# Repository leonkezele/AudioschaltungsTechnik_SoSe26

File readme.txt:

Bestellliste vom 22. 05. von Leon an Herr Tschirley
  - Bourns PTA4543-2015CPA103 - Fader: 10k log (Mouser Nr. 652-PTA4543-10K) mid. 10 Sück
  - Poti Alps RK09K 100k Single (Mouser Nr. 688-RK09K110K15C0104) mind. 10 Stück
  - Poti Alps RK09L 10k Dual (Mouser Nr. 688-RK09L1140A5E) mind. 30 Stück
  - J111 SOT23 (Mouser Nr. 512-MMBFJ111) mind. 10 Stück
  - 2917 Tantalelko 100u (mouser Nr. 80-T491D107K004) mind. 10 Stück
  - NE5532 SOIC-8 (Mouser Nr. 595-NE5532DR) (75 Stück)
  - LED THT mit V_f=3V (Mouser Nr. 941-C503BBANCY0C0462) (10 Stück)
  - Diode LL4148 Mini-MELF (Mouser Nr. 821-LL4148L0G) (20 Stück)
  - Schottky-Diode SOD-123: 1N5819HW (Mouser Nr. 621-1N5819HW-F) (20 Stück)

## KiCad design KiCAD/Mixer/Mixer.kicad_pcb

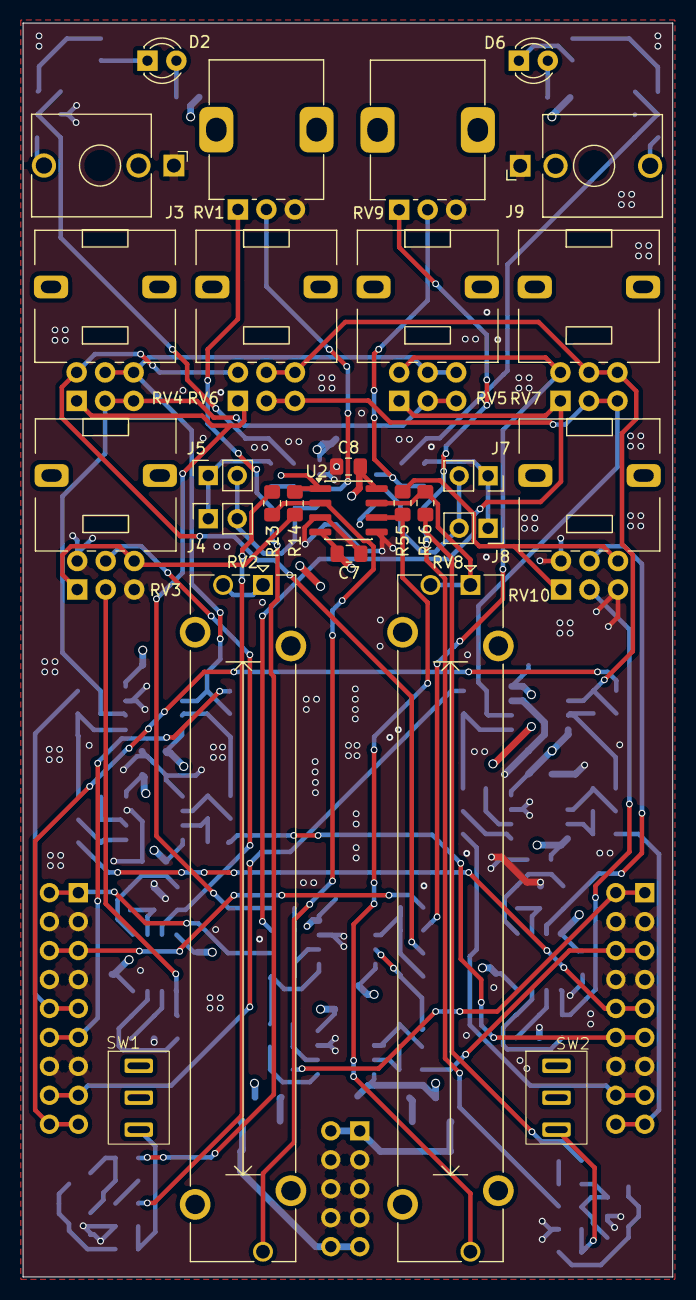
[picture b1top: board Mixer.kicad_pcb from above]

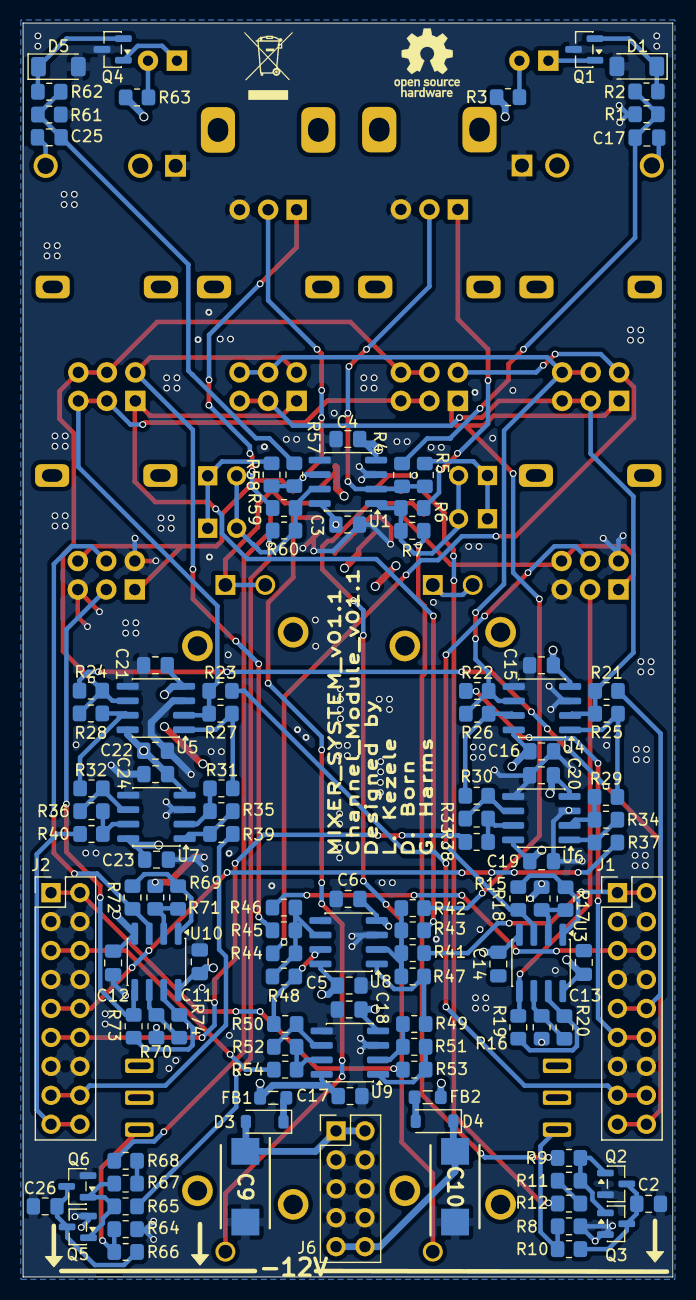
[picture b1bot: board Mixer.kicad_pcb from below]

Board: 4 copper layers, 57.0 x 110.0 mm, 145 parts (118 on the bottom side), 95 nets.

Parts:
C2, C26: 220n; C_0805_2012Metric_Pad1.18x1.45mm_HandSolder
C3, C4, C5, C6, C7, C8, C11, C12, C13, C14, C15, C16, C17, C18, C19, C20, C21, C22, C23, C24: 100n; C_0805_2012Metric_Pad1.18x1.45mm_HandSolder
C9, C10: 100u; CAPPM7343X310N
C17#2, C25: 2u; C_0805_2012Metric_Pad1.18x1.45mm_HandSolder
D1, D5: 1N4148; D_MiniMELF
D2, D6: LED; LED_D3.0mm
D3, D4: 1N5711; D_SOD-123
FB1, FB2: FerriteBead; L_0805_2012Metric_Pad1.05x1.20mm_HandSolder
J1, J2: Conn_02x09_Odd_Even; PinHeader_2x09_P2.54mm_Vertical
J3, J9: AudioJack2; Jack_3.5mm_QingPu_WQP-PJ398SM_Vertical_CircularHoles
J4, J5, J7, J8: Conn_01x02_Socket; PinSocket_1x02_P2.54mm_Vertical
J6: Conn_02x05_Odd_Even; PinHeader_2x05_P2.54mm_Vertical
Q1, Q4: NPN; SOT-23
Q2, Q3, Q5, Q6: MMBFJ111; SOT-23
R1, R61: 5k; R_0805_2012Metric_Pad1.20x1.40mm_HandSolder
R2, R10, R62, R66: 100k; R_0805_2012Metric_Pad1.20x1.40mm_HandSolder
R3, R63: 4,7k; R_0805_2012Metric_Pad1.20x1.40mm_HandSolder
R4, R57: 10K; R_0805_2012Metric_Pad1.20x1.40mm_HandSolder
R5, R58: 8k6; R_0805_2012Metric_Pad1.20x1.40mm_HandSolder
R6, R8, R13, R21, R22, R23, R24, R25, R26, R27, R28, R55, R59, R64: 10k; R_0805_2012Metric_Pad1.20x1.40mm_HandSolder
R7, R12, R14, R37, R38, R39, R40, R53, R54, R56, R60, R68: 0R; R_0805_2012Metric_Pad1.20x1.40mm_HandSolder
R9, R11, R65, R67: 2k2; R_0805_2012Metric_Pad1.20x1.40mm_HandSolder
R15, R16, R18, R19, R69, R70, R72, R73: 3k3; R_0805_2012Metric_Pad1.20x1.40mm_HandSolder
R17, R20, R29, R30, R31, R32, R33, R34, R35, R36, R41, R42, R43, R44, R45, R46, R47, R48, R49, R50, R51, R52, R71, R74: 1k; R_0805_2012Metric_Pad1.20x1.40mm_HandSolder
RV1, RV9: 100K; Potentiometer_Alps_RK09K_Single_Vertical
RV2: 10k; Potentiometer_Bourns_PTA4543_Single_Slide
RV3, RV4, RV5, RV6, RV7, RV10: 10k; Potentiometer_Alps_RK09L_Double_Vertical
RV8: R_Potentiometer; Potentiometer_Bourns_PTA4543_Single_Slide
SW1, SW2: SW_MEC_5G; Switch BHT
U1, U2, U3, U4, U5, U6, U7, U8, U9, U10: NE5532; SOIC-8_3.9x4.9mm_P1.27mm

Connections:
/Channel/+12V: C3.2, C5.2, C7.2, C11.2, C13.2, C15.2, C17.2, C19.2, C21.2, C23.2, FB1.1, R3.1, R63.1, U1.8 (V+), U2.4 (V-), U3.8 (V+), U4.4 (V-), U5.4 (V-), U6.8 (V+), U7.8 (V+), U8.8 (V+), U9.8 (V+), U10.8 (V+)
/Channel/-12V: C4.2, C6.2, C8.2, C12.2, C14.2, C16.2, C18.2, C20.2, C22.2, C24.2, FB2.2, SW1.1 (A), SW1.2 (A), SW2.1 (A), SW2.2 (A), U1.4 (V-), U2.8 (V+), U3.4 (V-), U4.8 (V+), U5.8 (V+), U6.4 (V-), U7.4 (V-), U8.4 (V-), U9.4 (V-), U10.4 (V-)
/Channel/Ch1_outL: R42.1, RV4.1, RV6.1
/Channel/Ch1_outR: R44.1, RV4.4, RV6.4
/Channel/Ch2_outL: R43.1, RV5.1, RV7.1
/Channel/Ch2_outR: R45.1, RV5.4, RV7.4
/Channel/Fader1/fader_in: R55.1, RV10.1, RV10.6
/Channel/Fader1/fader_out: R56.1, R68.1
/Channel/Fader/fader_in: R12.1, R13.1
/Channel/Fader/fader_out: R14.1, RV3.1, RV3.6
/Channel/Gain1/gain_in: C25.2, R57.1, R61.2, R62.1
/Channel/Gain1/gain_out: R60.1, R65.1
/Channel/Gain/gain_in: C17#2.2, R1.2, R2.1, R4.1
/Channel/Gain/gain_out: R7.1, R9.1
/Channel/Pan1/pan_outL: R71.2, R72.2, U10.1
/Channel/Pan1/pan_outR: R73.2, R74.2, U10.7
/Channel/Pan/pan_outL: R17.2, R18.2, U3.1
/Channel/Pan/pan_outR: R19.2, R20.2, U3.7
/Channel/main_mixL: J2.1, J2.2, R53.1
/Channel/main_mixR: J2.5, J2.6, R54.1
/Channel/pre_mixL: J1.1, J1.2, R41.1
/Channel/pre_mixR: J1.5, J1.6, R46.1
/Channel/pre_send1L: J1.9, J1.10, R21.1
/Channel/pre_send1R: J1.11, J1.12, R22.1
/Channel/pre_send2L: J1.15, J1.16, R23.1
/Channel/pre_send2R: J1.17, J1.18, R24.1
/Channel/send_out1L: J2.9, J2.10, R37.1
/Channel/send_out1R: J2.11, J2.12, R38.1
/Channel/send_out2L: J2.15, J2.16, R39.1
/Channel/send_out2R: J2.17, J2.18, R40.1
GND: C2.2, C3.1, C4.1, C5.1, C6.1, C7.1, C8.1, C9.2, C10.1, C11.1, C12.1, C15.1, C16.1, C17.1, C18.1, C19.1, C20.1, C21.1, C22.1, C23.1, C24.1, C26.2, D1.2 (A), D5.2 (A), J1.3, J1.4, J1.7, J1.8, J1.13, J1.14, J2.3, J2.4, J2.7, J2.8, J2.13, J2.14, J3.S, J6.3, J6.4, J6.5, J6.6, J6.7, J6.8, J9.S, Q1.3 (E), Q2.2 (S), Q3.2 (S), Q4.3 (E), Q5.2 (S), Q6.2 (S), R1.1, R8.1, R15.2, R16.1, R61.1, R64.1, R69.2, R70.1, RV1.3, RV3.3, RV3.4, RV9.3, RV10.3, RV10.4, U1.3 (+), U1.5 (+), U2.3 (+), U2.5 (+), U4.3 (+), U4.5 (+), U5.3 (+), U5.5 (+), U6.3 (+), U6.5 (+), U7.3 (+), U7.5 (+), U8.3 (+), U8.5 (+), U9.3 (+), U9.5 (+)
unnamed: C17#2.1, J3.T
unnamed: C25.1, J9.T
unnamed: D1.1 (K), Q1.2 (B), R2.2
unnamed: D2.2 (A), R3.2
unnamed: D2.1 (K), Q1.1 (C)
unnamed: C9.1, D3.2 (A), J6.1, J6.2
unnamed: D3.1 (K), FB1.2
unnamed: D4.2 (A), FB2.1
unnamed: C10.2, D4.1 (K), J6.9, J6.10
unnamed: D5.1 (K), Q4.2 (B), R62.2
unnamed: D6.2 (A), R63.2
unnamed: D6.1 (K), Q4.1 (C)
unnamed: J4.1, J5.1, R5.2
unnamed: J4.2, J5.2, R6.1, R7.2, U1.1
unnamed: J7.1, J8.1, R58.2
unnamed: J7.2, J8.2, R59.1, R60.2, U1.7
unnamed: Q2.1 (D), Q3.1 (D), R9.2, R11.1
unnamed: C2.1, Q2.3 (G), Q3.3 (G), R10.2
unnamed: Q5.1 (D), Q6.1 (D), R65.2, R67.1
unnamed: C26.1, Q5.3 (G), Q6.3 (G), R66.2
unnamed: R6.2, RV1.1
unnamed: R8.2, R10.1, SW1.3 (B)
unnamed: R11.2, R12.2
unnamed: R14.2, RV2.1, RV2.2, U2.1
unnamed: R25.2, R29.1, U4.1
unnamed: R26.2, R30.1, U4.7
unnamed: R27.2, R31.1, U5.1
unnamed: R28.2, R32.1, U5.7
unnamed: R33.2, R38.2, U6.7
unnamed: R34.2, R37.2, U6.1
unnamed: R35.2, R39.2, U7.1
unnamed: R36.2, R40.2, U7.7
unnamed: R47.2, R49.1, U8.1
unnamed: R48.2, R50.1, U8.7
unnamed: R51.2, R53.2, U9.1
unnamed: R52.2, R54.2, U9.7
unnamed: R56.2, RV8.1, RV8.2, U2.7
unnamed: R59.2, RV9.1
unnamed: R64.2, R66.1, SW2.3 (B)
unnamed: R67.2, R68.2
unnamed: R4.2, R5.1, RV1.2, U1.2 (-)
unnamed: R57.2, R58.1, RV9.2, U1.6 (-)
unnamed: R13.2, RV2.3, U2.2 (-)
unnamed: R55.2, RV8.3, U2.6 (-)
unnamed: R18.1, RV3.5, U3.3 (+)
unnamed: R15.1, R17.1, U3.2 (-)
unnamed: R19.1, RV3.2, U3.5 (+)
unnamed: R16.2, R20.1, U3.6 (-)
unnamed: R21.2, R25.1, RV4.2, RV4.3, RV5.2, RV5.3, U4.2 (-)
unnamed: R22.2, R26.1, RV4.5, RV4.6, RV5.5, RV5.6, U4.6 (-)
unnamed: R23.2, R27.1, RV6.2, RV6.3, RV7.2, RV7.3, U5.2 (-)
unnamed: R24.2, R28.1, RV6.5, RV6.6, RV7.5, RV7.6, U5.6 (-)
unnamed: R29.2, R34.1, U6.2 (-)
unnamed: R30.2, R33.1, U6.6 (-)
unnamed: R31.2, R35.1, U7.2 (-)
unnamed: R32.2, R36.1, U7.6 (-)
unnamed: R41.2, R42.2, R43.2, R47.1, U8.2 (-)
unnamed: R44.2, R45.2, R46.2, R48.1, U8.6 (-)
unnamed: R49.2, R51.1, U9.2 (-)
unnamed: R50.2, R52.1, U9.6 (-)
unnamed: R72.1, RV10.5, U10.3 (+)
unnamed: R69.1, R71.1, U10.2 (-)
unnamed: R73.1, RV10.2, U10.5 (+)
unnamed: R70.2, R74.1, U10.6 (-)

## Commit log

2026-04-25 readme hinzugefügt. Für Doku, Todos usw
2026-04-30 Power Bus, Footprints, Audio Bus
2026-04-30 Readme edit
2026-05-02 added second channel and footprints / created PCB desing...might make PCB bit bigger
2026-05-02 annotation
2026-05-09 Cs an OPV-Strom, Anpassung clicklessmute,...
2026-05-14 überarbeitete Schaltung und PCB Desing...v1.0 FERTIG
2026-05-15 Main Modul Schaltung
2026-05-17 Rework of schematic, with error fixes and reworked pcb
2026-05-22 Final PCB Version that got ordered from JLCPCB
2026-05-22 updated readme with part order list
